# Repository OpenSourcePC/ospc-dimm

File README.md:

# ospc-dimm
Open Source DIMM modules.

For a contribution guide, see CONTRIBUTING.md

## Folder format

`ospc-ddr[ddr version]-[dimmtype]-[number of ranks]r-x[data bus width of modules, comma seperated if mixed]-[S if SPD only, T if SPD + temp sensor]`

## Subprojects

`✔️: done ❓: needs verification, ❌: not done`

Projects marked for verification may not function properly.

 * `ospc-ddr4-udimm-1r-x16-t` : UDIMM, DDR4, 1 rank, x16 (96ball), SPD+Temp (Schematic ❓, PCB ❌)

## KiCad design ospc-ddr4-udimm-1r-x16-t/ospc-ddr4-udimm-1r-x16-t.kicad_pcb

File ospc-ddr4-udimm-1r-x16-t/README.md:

# ospc-ddr4-udimm-1r-x16-t

To-dos:
 * Schem verification.
 * PCB routing & resistor/capacitor positioning.

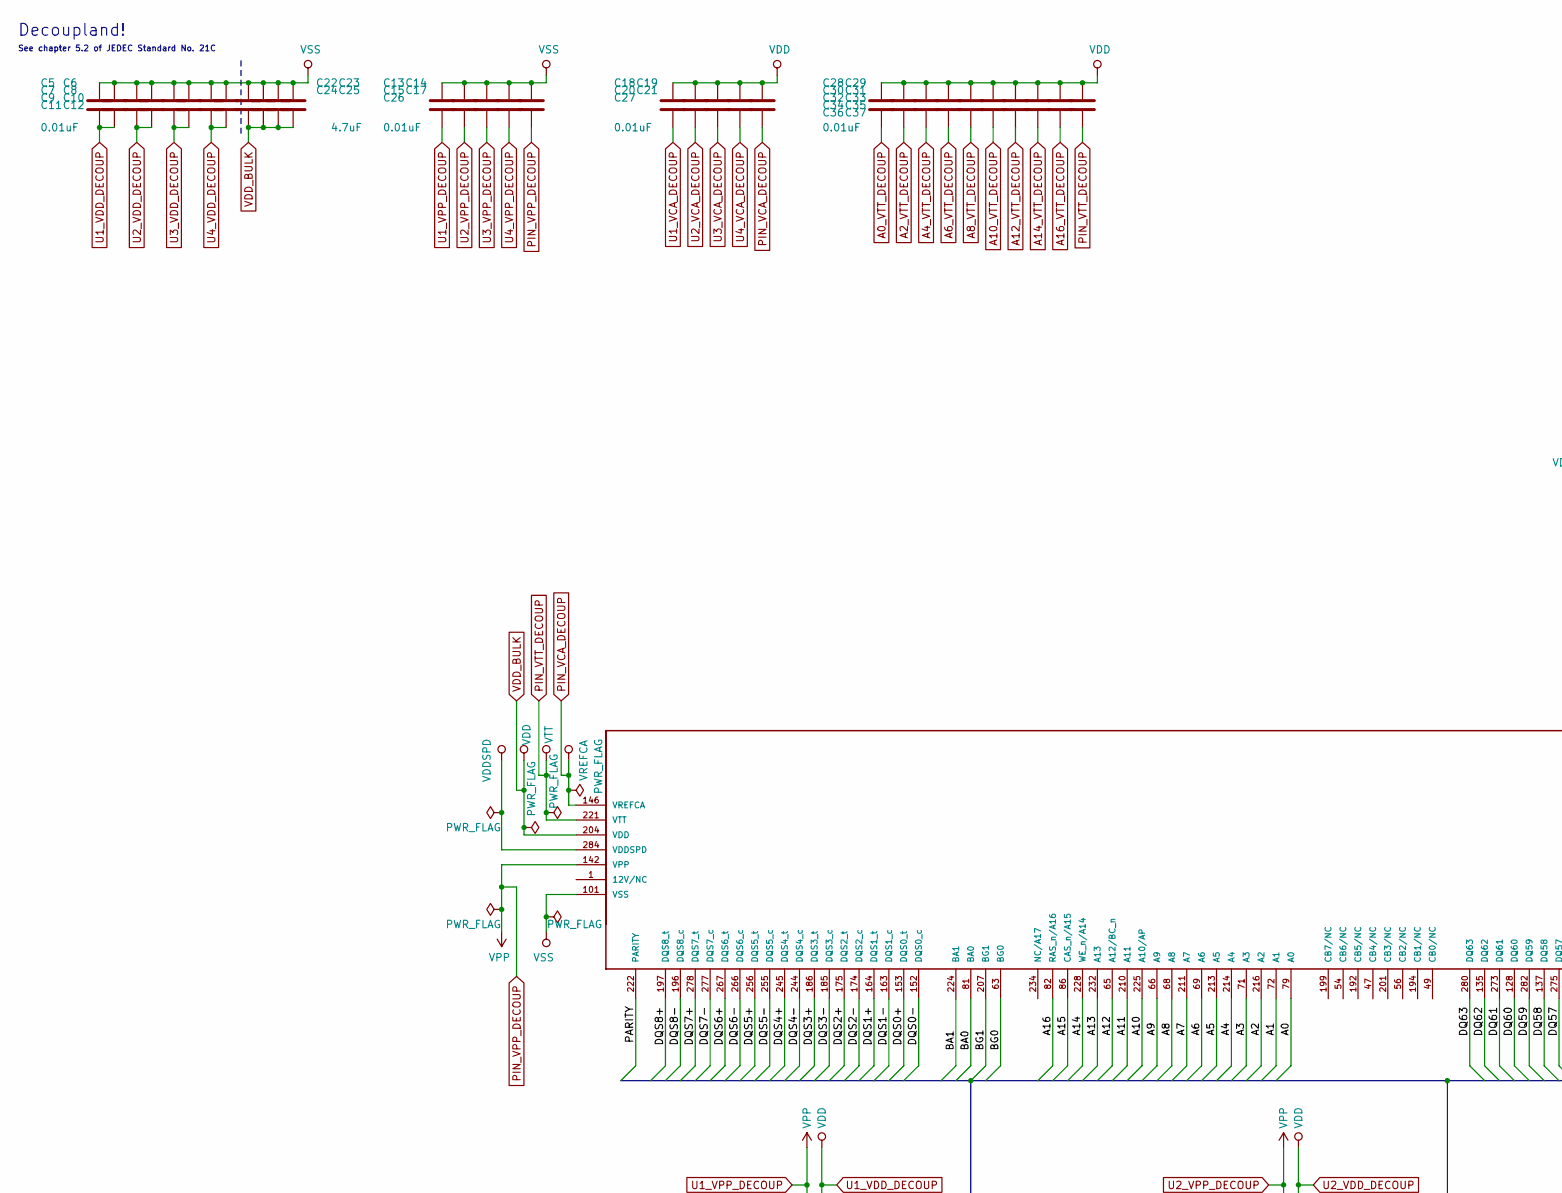
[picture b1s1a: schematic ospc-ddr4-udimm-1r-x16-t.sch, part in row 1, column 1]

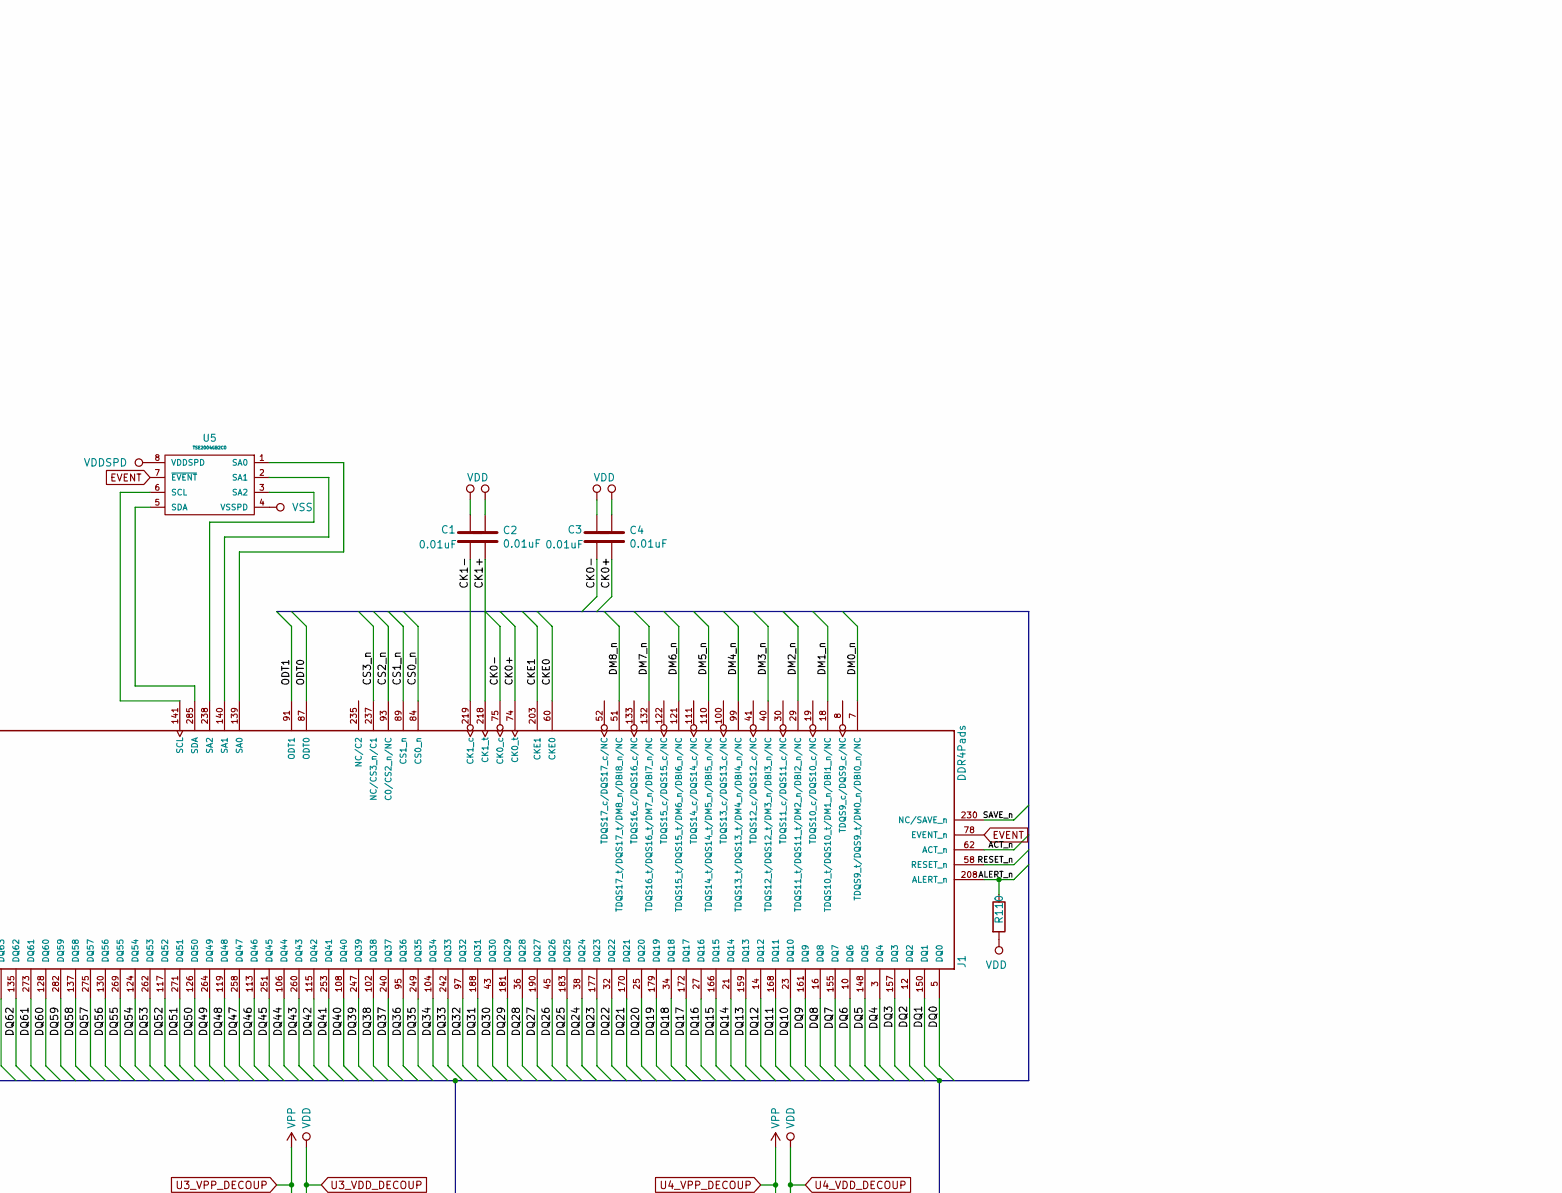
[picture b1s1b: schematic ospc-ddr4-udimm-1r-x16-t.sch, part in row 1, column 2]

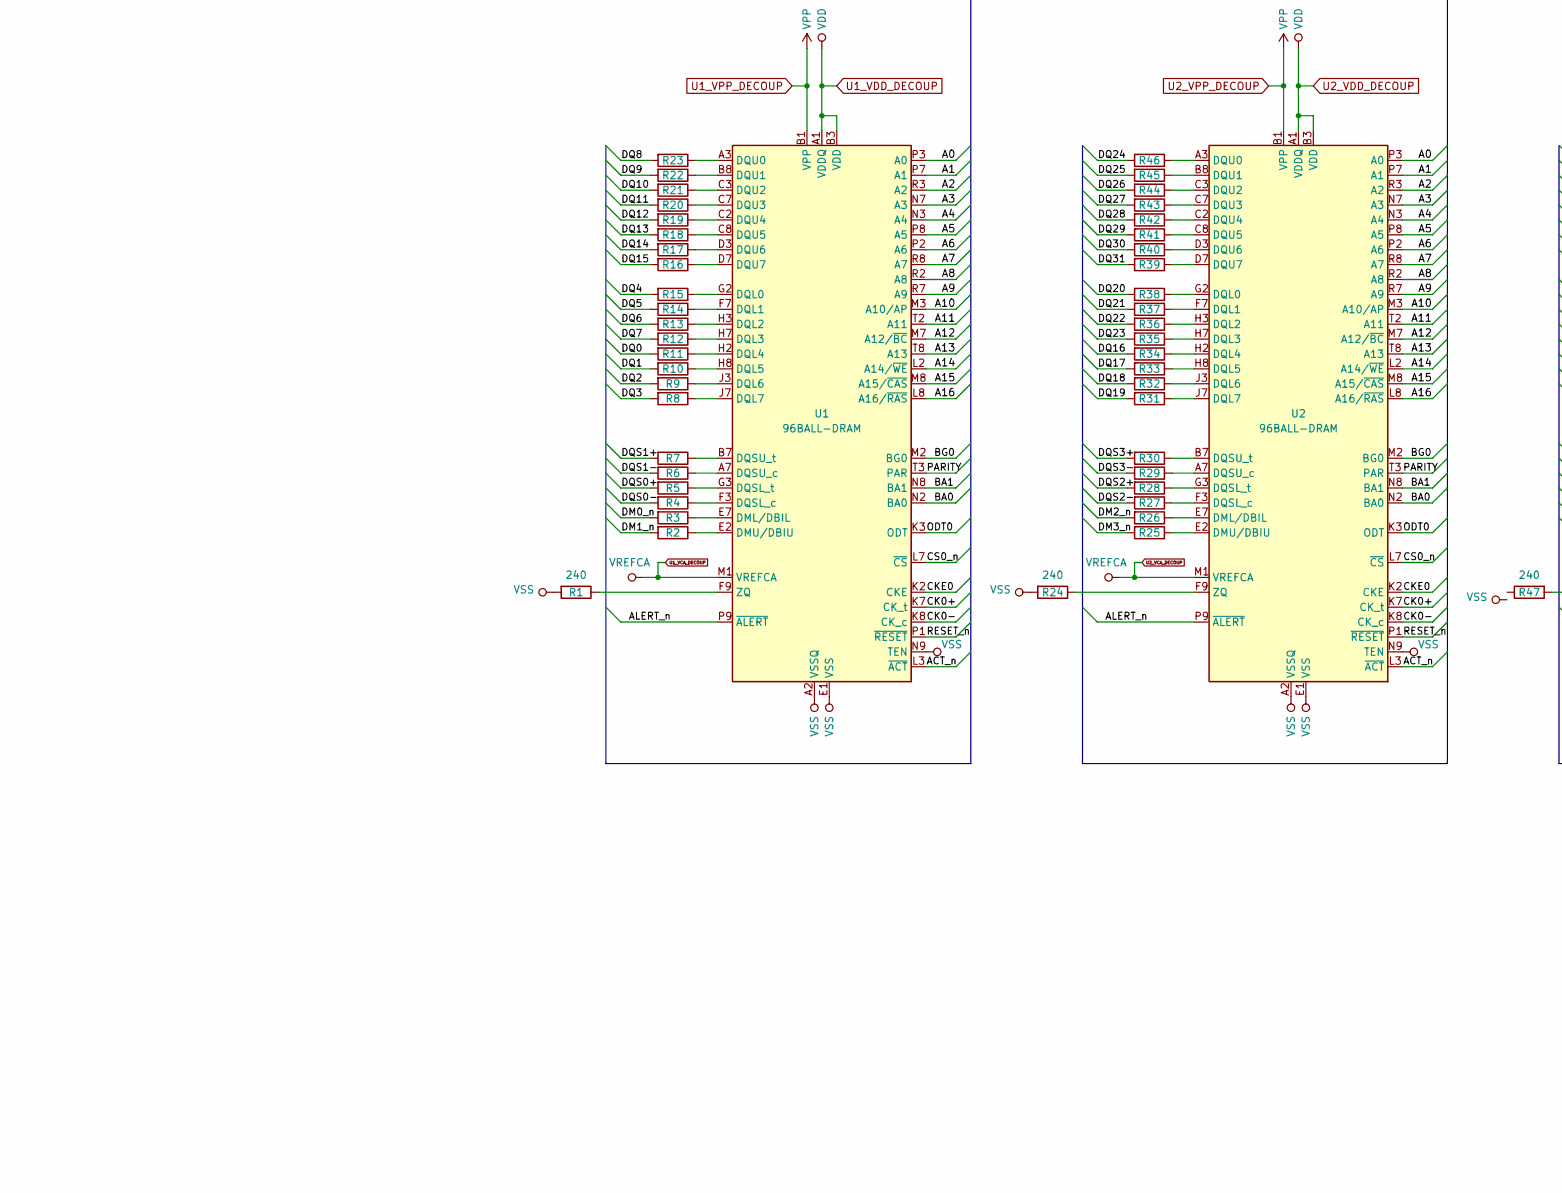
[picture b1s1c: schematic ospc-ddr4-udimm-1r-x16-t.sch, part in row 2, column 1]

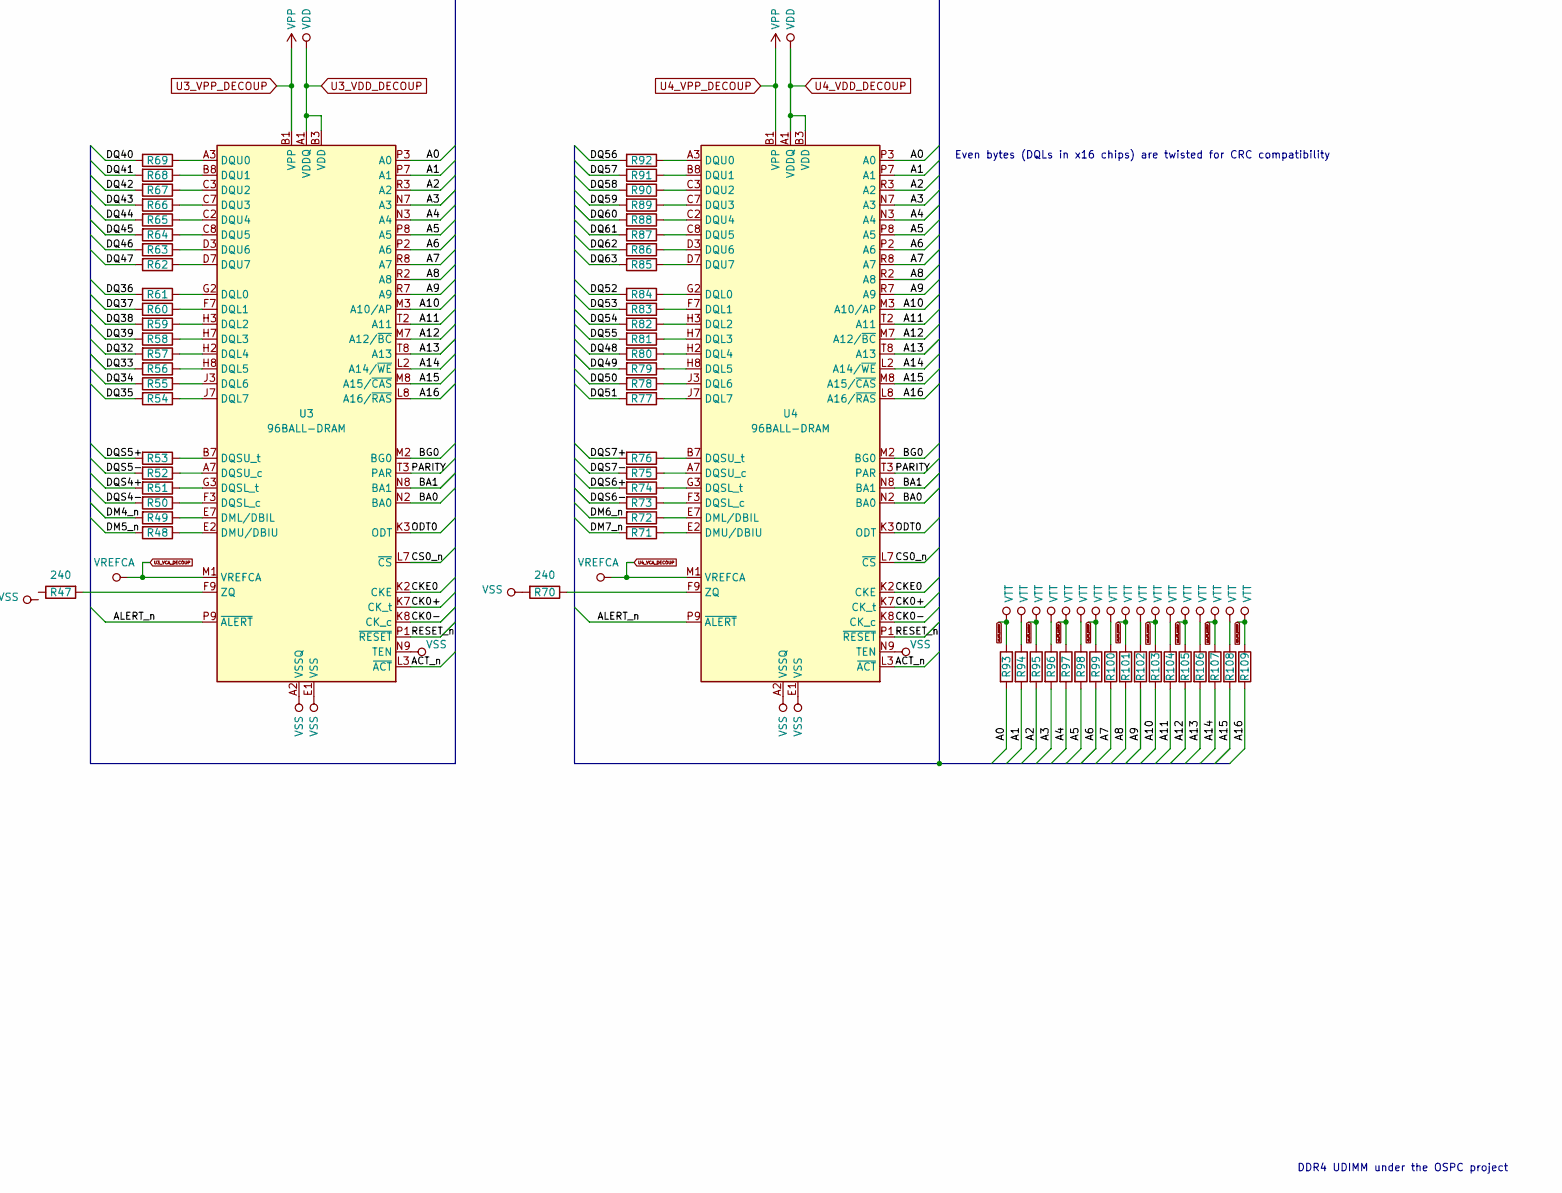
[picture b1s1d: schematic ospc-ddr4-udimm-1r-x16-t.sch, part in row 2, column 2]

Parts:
C1, C2, C3, C4, C5, C6, C7, C8, C9, C10, C11, C12, C13, C14, C15, C17, C18, C19, C20, C21, C26, C27, C28, C29, C30, C31, C32, C33, C34, C35, C36, C37: 0.01uF; C_0402_1005Metric
C22, C23, C24, C25: 4.7uF; C_0402_1005Metric
J1: DDR4Pads; DDR4_DIMM
R1, R24, R47, R70: 240; R_0402_1005Metric
R2, R3, R4, R5, R6, R7, R8, R9, R10, R11, R12, R13, R14, R15, R16, R17, R18, R19, R20, R21, R22, R23, R25, R26, R27, R28, R29, R30, R31, R32, R33, R34, R35, R36, R37, R38, R39, R40, R41, R42, R43, R44, R45, R46, R48, R49, R50, R51, R52, R53, R54, R55, R56, R57, R58, R59, R60, R61, R62, R63, R64, R65, R66, R67, R68, R69, R71, R72, R73, R74, R75, R76, R77, R78, R79, R80, R81, R82, R83, R84, R85, R86, R87, R88, R89, R90, R91, R92, R93, R94, R95, R96, R97, R98, R99, R100, R101, R102, R103, R104, R105, R106, R107, R108, R109, R110: 15; R_0402_1005Metric
U1, U2, U3, U4: 96BALL-DRAM; FBGA96
U5: TSE2004GB2C0; DFN-8-1EP_2x3mm_P0.5mm_EP0.61x2.2mm

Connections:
/A0: J1.79 (A0), R93.2, U1.P3 (A0), U2.P3 (A0), U3.P3 (A0), U4.P3 (A0)
/A1: J1.72 (A1), R94.2, U1.P7 (A1), U2.P7 (A1), U3.P7 (A1), U4.P7 (A1)
/A2: J1.216 (A2), R95.2, U1.R3 (A2), U2.R3 (A2), U3.R3 (A2), U4.R3 (A2)
/A3: J1.71 (A3), R96.2, U1.N7 (A3), U2.N7 (A3), U3.N7 (A3), U4.N7 (A3)
/A4: J1.214 (A4), R97.2, U1.N3 (A4), U2.N3 (A4), U3.N3 (A4), U4.N3 (A4)
/A5: J1.213 (A5), R98.2, U1.P8 (A5), U2.P8 (A5), U3.P8 (A5), U4.P8 (A5)
/A6: J1.69 (A6), R99.2, U1.P2 (A6), U2.P2 (A6), U3.P2 (A6), U4.P2 (A6)
/A7: J1.211 (A7), R100.2, U1.R8 (A7), U2.R8 (A7), U3.R8 (A7), U4.R8 (A7)
/A8: J1.68 (A8), R101.2, U1.R2 (A8), U2.R2 (A8), U3.R2 (A8), U4.R2 (A8)
/A9: J1.66 (A9), R102.2, U1.R7 (A9), U2.R7 (A9), U3.R7 (A9), U4.R7 (A9)
/A10: J1.225 (A10/AP), R103.2, U1.M3 (A10/AP), U2.M3 (A10/AP), U3.M3 (A10/AP), U4.M3 (A10/AP)
/A11: J1.210 (A11), R104.2, U1.T2 (A11), U2.T2 (A11), U3.T2 (A11), U4.T2 (A11)
/A12: J1.65 (A12/BC_n), R105.2, U1.M7 (A12/~BC), U2.M7 (A12/~BC), U3.M7 (A12/~BC), U4.M7 (A12/~BC)
/A13: J1.232 (A13), R106.2, U1.T8 (A13), U2.T8 (A13), U3.T8 (A13), U4.T8 (A13)
/A14: J1.228 (WE_n/A14), R107.2, U1.L2 (A14/~WE), U2.L2 (A14/~WE), U3.L2 (A14/~WE), U4.L2 (A14/~WE)
/A15: J1.86 (CAS_n/A15), R108.2, U1.M8 (A15/~CAS), U2.M8 (A15/~CAS), U3.M8 (A15/~CAS), U4.M8 (A15/~CAS)
/A16: J1.82 (RAS_n/A16), R109.2, U1.L8 (A16/~RAS), U2.L8 (A16/~RAS), U3.L8 (A16/~RAS), U4.L8 (A16/~RAS)
/ACT_n: J1.62 (ACT_n), U1.L3 (~ACT), U2.L3 (~ACT), U3.L3 (~ACT), U4.L3 (~ACT)
/ALERT_n: J1.208 (ALERT_n), R110.1, U1.P9 (~ALERT), U2.P9 (~ALERT), U3.P9 (~ALERT), U4.P9 (~ALERT)
/BA0: J1.81 (BA0), U1.N2 (BA0), U2.N2 (BA0), U3.N2 (BA0), U4.N2 (BA0)
/BA1: J1.224 (BA1), U1.N8 (BA1), U2.N8 (BA1), U3.N8 (BA1), U4.N8 (BA1)
/BG0: J1.63 (BG0), U1.M2 (BG0), U2.M2 (BG0), U3.M2 (BG0), U4.M2 (BG0)
/BG1: J1.207 (BG1)
/CK0+: C4.2, J1.74 (CK0_t), U1.K7 (CK_t), U2.K7 (CK_t), U3.K7 (CK_t), U4.K7 (CK_t)
/CK0-: C3.2, J1.75 (CK0_c), U1.K8 (CK_c), U2.K8 (CK_c), U3.K8 (CK_c), U4.K8 (CK_c)
/CK1+: C2.2, J1.218 (CK1_t)
/CK1-: C1.2, J1.219 (CK1_c)
/CKE0: J1.60 (CKE0), U1.K2 (CKE), U2.K2 (CKE), U3.K2 (CKE), U4.K2 (CKE)
/CKE1: J1.203 (CKE1)
/CS0_n: J1.84 (CS0_n), U1.L7 (~CS), U2.L7 (~CS), U3.L7 (~CS), U4.L7 (~CS)
/CS1_n: J1.89 (CS1_n)
/CS2_n: J1.93 (C0/CS2_n/NC)
/CS3_n: J1.237 (NC/CS3_n/C1)
/DM0_n: J1.7 (TDQS9_t/DQS9_t/DM0_n/DBI0_n/NC), R3.2
/DM1_n: J1.18 (TDQS10_t/DQS10_t/DM1_n/DBI1_n/NC), R2.2
/DM2_n: J1.29 (TDQS11_t/DQS11_t/DM2_n/DBI2_n/NC), R26.2
/DM3_n: J1.40 (TDQS12_t/DQS12_t/DM3_n/DBI3_n/NC), R25.2
/DM4_n: J1.99 (TDQS13_t/DQS13_t/DM4_n/DBI4_n/NC), R49.2
/DM5_n: J1.110 (TDQS14_t/DQS14_t/DM5_n/DBI5_n/NC), R48.2
/DM6_n: J1.121 (TDQS15_t/DQS15_t/DM6_n/DBI6_n/NC), R72.2
/DM7_n: J1.132 (TDQS16_t/DQS16_t/DM7_n/DBI7_n/NC), R71.2
/DM8_n: J1.51 (TDQS17_t/DQS17_t/DM8_n/DBI8_n/NC)
/DQ0: J1.5 (DQ0), R11.2
/DQ1: J1.150 (DQ1), R10.2
/DQ2: J1.12 (DQ2), R9.2
/DQ3: J1.157 (DQ3), R8.2
/DQ4: J1.3 (DQ4), R15.2
/DQ5: J1.148 (DQ5), R14.2
/DQ6: J1.10 (DQ6), R13.2
/DQ7: J1.155 (DQ7), R12.2
/DQ8: J1.16 (DQ8), R23.2
/DQ9: J1.161 (DQ9), R22.2
/DQ10: J1.23 (DQ10), R21.2
/DQ11: J1.168 (DQ11), R20.2
/DQ12: J1.14 (DQ12), R19.2
/DQ13: J1.159 (DQ13), R18.2
/DQ14: J1.21 (DQ14), R17.2
/DQ15: J1.166 (DQ15), R16.2
/DQ16: J1.27 (DQ16), R34.2
/DQ17: J1.172 (DQ17), R33.2
/DQ18: J1.34 (DQ18), R32.2
/DQ19: J1.179 (DQ19), R31.2
/DQ20: J1.25 (DQ20), R38.2
/DQ21: J1.170 (DQ21), R37.2
/DQ22: J1.32 (DQ22), R36.2
/DQ23: J1.177 (DQ23), R35.2
/DQ24: J1.38 (DQ24), R46.2
/DQ25: J1.183 (DQ25), R45.2
/DQ26: J1.45 (DQ26), R44.2
/DQ27: J1.190 (DQ27), R43.2
/DQ28: J1.36 (DQ28), R42.2
/DQ29: J1.181 (DQ29), R41.2
/DQ30: J1.43 (DQ30), R40.2
/DQ31: J1.188 (DQ31), R39.2
/DQ32: J1.97 (DQ32), R57.2
/DQ33: J1.242 (DQ33), R56.2
/DQ34: J1.104 (DQ34), R55.1
/DQ35: J1.249 (DQ35), R54.2
/DQ36: J1.95 (DQ36), R61.2
/DQ37: J1.240 (DQ37), R60.2
/DQ38: J1.102 (DQ38), R59.2
/DQ39: J1.247 (DQ39), R58.2
/DQ40: J1.108 (DQ40), R69.2
/DQ41: J1.253 (DQ41), R68.2
/DQ42: J1.115 (DQ42), R67.2
/DQ43: J1.260 (DQ43), R66.2
/DQ44: J1.106 (DQ44), R65.2
/DQ45: J1.251 (DQ45), R64.2
/DQ46: J1.113 (DQ46), R63.2
/DQ47: J1.258 (DQ47), R62.2
/DQ48: J1.119 (DQ48), R80.2
/DQ49: J1.264 (DQ49), R79.2
/DQ50: J1.126 (DQ50), R78.2
/DQ51: J1.271 (DQ51), R77.2
/DQ52: J1.117 (DQ52), R84.2
/DQ53: J1.262 (DQ53), R83.2
/DQ54: J1.124 (DQ54), R82.2
/DQ55: J1.269 (DQ55), R81.2
/DQ56: J1.130 (DQ56), R92.2
/DQ57: J1.275 (DQ57), R91.2
/DQ58: J1.137 (DQ58), R90.2
/DQ59: J1.282 (DQ59), R89.2
/DQ60: J1.128 (DQ60), R88.2
/DQ61: J1.273 (DQ61), R87.2
/DQ62: J1.135 (DQ62), R86.2
/DQ63: J1.280 (DQ63), R85.2
/DQS0+: J1.153 (DQS0_t), R5.2
/DQS0-: J1.152 (DQS0_c), R4.2
/DQS1+: J1.164 (DQS1_t), R7.2
/DQS1-: J1.163 (DQS1_c), R6.2
/DQS2+: J1.175 (DQS2_t), R28.2
/DQS2-: J1.174 (DQS2_c), R27.2
/DQS3+: J1.186 (DQS3_t), R30.2
/DQS3-: J1.185 (DQS3_c), R29.2
/DQS4+: J1.245 (DQS4_t), R51.2
/DQS4-: J1.244 (DQS4_c), R50.2
/DQS5+: J1.256 (DQS5_t), R53.2
/DQS5-: J1.255 (DQS5_c), R52.2
/DQS6+: J1.267 (DQS6_t), R74.2
/DQS6-: J1.266 (DQS6_c), R73.2
/DQS7+: J1.278 (DQS7_t), R76.2
/DQS7-: J1.277 (DQS7_c), R75.2
/DQS8+: J1.197 (DQS8_t)
/DQS8-: J1.196 (DQS8_c)
/ODT0: J1.87 (ODT0), U1.K3 (ODT), U2.K3 (ODT), U3.K3 (ODT), U4.K3 (ODT)
/ODT1: J1.91 (ODT1)
/PARITY: J1.222 (PARITY), U1.T3 (PAR), U2.T3 (PAR), U3.T3 (PAR), U4.T3 (PAR)
/RESET_n: J1.58 (RESET_n), U1.P1 (~RESET), U2.P1 (~RESET), U3.P1 (~RESET), U4.P1 (~RESET)
/SAVE_n: J1.230 (NC/SAVE_n)
A0_VTT_DECOUP: C28.2, C29.2, C30.2, C31.2, C32.2, C33.2, C34.2, C35.2, C36.2, C37.2, J1.77 (VTT), J1.221 (VTT), R93.1, R94.1, R95.1, R96.1, R97.1, R98.1, R99.1, R100.1, R101.1, R102.1, R103.1, R104.1, R105.1, R106.1, R107.1, R108.1, R109.1
EVENT: J1.78 (EVENT_n), U5.7 (~EVENT)
unnamed: J1.1 (12V/NC), J1.145 (12V/NC)
unnamed: J1.139 (SA0), U5.1 (SA0)
unnamed: J1.140 (SA1), U5.2 (SA1)
unnamed: J1.141 (SCL), U5.6 (SCL)
unnamed: J1.144 (RFU), J1.205 (RFU), J1.227 (RFU)
unnamed: J1.238 (SA2), U5.3 (SA2)
unnamed: J1.285 (SDA), U5.5 (SDA)
unnamed: R1.1, U1.F9 (ZQ)
unnamed: R2.1, U1.E2 (DMU/DBIU)
unnamed: R3.1, U1.E7 (DML/DBIL)
unnamed: R4.1, U1.F3 (DQSL_c)
unnamed: R5.1, U1.G3 (DQSL_t)
unnamed: R6.1, U1.A7 (DQSU_c)
unnamed: R7.1, U1.B7 (DQSU_t)
unnamed: R8.1, U1.J7 (DQL7)
unnamed: R9.1, U1.J3 (DQL6)
unnamed: R10.1, U1.H8 (DQL5)
unnamed: R11.1, U1.H2 (DQL4)
unnamed: R12.1, U1.H7 (DQL3)
unnamed: R13.1, U1.H3 (DQL2)
unnamed: R14.1, U1.F7 (DQL1)
unnamed: R15.1, U1.G2 (DQL0)
unnamed: R16.1, U1.D7 (DQU7)
unnamed: R17.1, U1.D3 (DQU6)
unnamed: R18.1, U1.C8 (DQU5)
unnamed: R19.1, U1.C2 (DQU4)
unnamed: R20.1, U1.C7 (DQU3)
unnamed: R21.1, U1.C3 (DQU2)
unnamed: R22.1, U1.B8 (DQU1)
unnamed: R23.1, U1.A3 (DQU0)
unnamed: R24.1, U2.F9 (ZQ)
unnamed: R25.1, U2.E2 (DMU/DBIU)
unnamed: R26.1, U2.E7 (DML/DBIL)
unnamed: R27.1, U2.F3 (DQSL_c)
unnamed: R28.1, U2.G3 (DQSL_t)
unnamed: R29.1, U2.A7 (DQSU_c)
unnamed: R30.1, U2.B7 (DQSU_t)
unnamed: R31.1, U2.J7 (DQL7)
unnamed: R32.1, U2.J3 (DQL6)
unnamed: R33.1, U2.H8 (DQL5)
unnamed: R34.1, U2.H2 (DQL4)
unnamed: R35.1, U2.H7 (DQL3)
unnamed: R36.1, U2.H3 (DQL2)
unnamed: R37.1, U2.F7 (DQL1)
unnamed: R38.1, U2.G2 (DQL0)
unnamed: R39.1, U2.D7 (DQU7)
unnamed: R40.1, U2.D3 (DQU6)
unnamed: R41.1, U2.C8 (DQU5)
unnamed: R42.1, U2.C2 (DQU4)
unnamed: R43.1, U2.C7 (DQU3)
unnamed: R44.1, U2.C3 (DQU2)
unnamed: R45.1, U2.B8 (DQU1)
unnamed: R46.1, U2.A3 (DQU0)
unnamed: R47.2, U3.F9 (ZQ)
unnamed: R48.1, U3.E2 (DMU/DBIU)
unnamed: R49.1, U3.E7 (DML/DBIL)
unnamed: R50.1, U3.F3 (DQSL_c)
unnamed: R51.1, U3.G3 (DQSL_t)
unnamed: R52.1, U3.A7 (DQSU_c)
unnamed: R53.1, U3.B7 (DQSU_t)
unnamed: R54.1, U3.J7 (DQL7)
unnamed: R55.2, U3.J3 (DQL6)
unnamed: R56.1, U3.H8 (DQL5)
unnamed: R57.1, U3.H2 (DQL4)
unnamed: R58.1, U3.H7 (DQL3)
unnamed: R59.1, U3.H3 (DQL2)
unnamed: R60.1, U3.F7 (DQL1)
unnamed: R61.1, U3.G2 (DQL0)
unnamed: R62.1, U3.D7 (DQU7)
unnamed: R63.1, U3.D3 (DQU6)
unnamed: R64.1, U3.C8 (DQU5)
unnamed: R65.1, U3.C2 (DQU4)
unnamed: R66.1, U3.C7 (DQU3)
unnamed: R67.1, U3.C3 (DQU2)
unnamed: R68.1, U3.B8 (DQU1)
unnamed: R69.1, U3.A3 (DQU0)
unnamed: R70.1, U4.F9 (ZQ)
unnamed: R71.1, U4.E2 (DMU/DBIU)
unnamed: R72.1, U4.E7 (DML/DBIL)
unnamed: R73.1, U4.F3 (DQSL_c)
unnamed: R74.1, U4.G3 (DQSL_t)
unnamed: R75.1, U4.A7 (DQSU_c)
unnamed: R76.1, U4.B7 (DQSU_t)
unnamed: R77.1, U4.J7 (DQL7)
unnamed: R78.1, U4.J3 (DQL6)
unnamed: R79.1, U4.H8 (DQL5)
unnamed: R80.1, U4.H2 (DQL4)
unnamed: R81.1, U4.H7 (DQL3)
unnamed: R82.1, U4.H3 (DQL2)
unnamed: R83.1, U4.F7 (DQL1)
unnamed: R84.1, U4.G2 (DQL0)
unnamed: R85.1, U4.D7 (DQU7)
unnamed: R86.1, U4.D3 (DQU6)
unnamed: R87.1, U4.C8 (DQU5)
unnamed: R88.1, U4.C2 (DQU4)
unnamed: R89.1, U4.C7 (DQU3)
unnamed: R90.1, U4.C3 (DQU2)
unnamed: R91.1, U4.B8 (DQU1)
unnamed: R92.1, U4.A3 (DQU0)
PIN_VCA_DECOUP: C18.2, C19.2, C20.2, C21.2, C27.2, J1.146 (VREFCA), U1.M1 (VREFCA), U2.M1 (VREFCA), U3.M1 (VREFCA), U4.M1 (VREFCA)
PIN_VPP_DECOUP: C13.2, C14.2, C15.2, C17.2, C26.2, J1.142 (VPP), J1.143 (VPP), J1.286 (VPP), J1.287 (VPP), J1.288 (VPP), U1.B1 (VPP), U1.R9 (VPP), U2.B1 (VPP), U2.R9 (VPP), U3.B1 (VPP), U3.R9 (VPP), U4.B1 (VPP), U4.R9 (VPP)
U1_VDD_DECOUP: C1.1, C2.1, C3.1, C4.1, C5.2, C6.2, C7.2, C8.2, C9.2, C10.2, C11.2, C12.2, C18.1, C19.1, C20.1, C21.1, C22.2, C23.2, C24.2, C25.2, C27.1, C28.1, C29.1, C30.1, C31.1, C32.1, C33.1, C34.1, C35.1, C36.1, C37.1, J1.59 (VDD), J1.61 (VDD), J1.64 (VDD), J1.67 (VDD), J1.70 (VDD), J1.73 (VDD), J1.76 (VDD), J1.80 (VDD), J1.83 (VDD), J1.85 (VDD), J1.88 (VDD), J1.90 (VDD), J1.92 (VDD), J1.204 (VDD), J1.206 (VDD), J1.209 (VDD), J1.212 (VDD), J1.215 (VDD), J1.217 (VDD), J1.220 (VDD), J1.223 (VDD), J1.226 (VDD), J1.229 (VDD), J1.231 (VDD), J1.233 (VDD), J1.236 (VDD), R110.2, U1.A1 (VDDQ), U1.A9 (VDDQ), U1.B3 (VDD), U1.B9 (VDD), U1.C1 (VDDQ), U1.D1 (VDD), U1.D9 (VDDQ), U1.F2 (VDDQ), U1.F8 (VDDQ), U1.G1 (VDDQ), U1.G7 (VDD), U1.G9 (VDDQ), U1.J1 (VDD), U1.J2 (VDDQ), U1.J8 (VDDQ), U1.J9 (VDD), U1.L1 (VDD), U1.L9 (VDD), U1.R1 (VDD), U1.T9 (VDD), U2.A1 (VDDQ), U2.A9 (VDDQ), U2.B3 (VDD), U2.B9 (VDD), U2.C1 (VDDQ), U2.D1 (VDD), U2.D9 (VDDQ), U2.F2 (VDDQ), U2.F8 (VDDQ), U2.G1 (VDDQ), U2.G7 (VDD), U2.G9 (VDDQ), U2.J1 (VDD), U2.J2 (VDDQ), U2.J8 (VDDQ), U2.J9 (VDD), U2.L1 (VDD), U2.L9 (VDD), U2.R1 (VDD), U2.T9 (VDD), U3.A1 (VDDQ), U3.A9 (VDDQ), U3.B3 (VDD), U3.B9 (VDD), U3.C1 (VDDQ), U3.D1 (VDD), U3.D9 (VDDQ), U3.F2 (VDDQ), U3.F8 (VDDQ), U3.G1 (VDDQ), U3.G7 (VDD), U3.G9 (VDDQ), U3.J1 (VDD), U3.J2 (VDDQ), U3.J8 (VDDQ), U3.J9 (VDD), U3.L1 (VDD), U3.L9 (VDD), U3.R1 (VDD), U3.T9 (VDD), U4.A1 (VDDQ), U4.A9 (VDDQ), U4.B3 (VDD), U4.B9 (VDD), U4.C1 (VDDQ), U4.D1 (VDD), U4.D9 (VDDQ), U4.F2 (VDDQ), U4.F8 (VDDQ), U4.G1 (VDDQ), U4.G7 (VDD), U4.G9 (VDDQ), U4.J1 (VDD), U4.J2 (VDDQ), U4.J8 (VDDQ), U4.J9 (VDD), U4.L1 (VDD), U4.L9 (VDD), U4.R1 (VDD), U4.T9 (VDD)
VDDSPD: J1.284 (VDDSPD), U5.8 (VDDSPD)
VSS: C5.1, C6.1, C7.1, C8.1, C9.1, C10.1, C11.1, C12.1, C13.1, C14.1, C15.1, C17.1, C22.1, C23.1, C24.1, C25.1, C26.1, J1.2 (VSS), J1.4 (VSS), J1.6 (VSS), J1.9 (VSS), J1.11 (VSS), J1.13 (VSS), J1.15 (VSS), J1.17 (VSS), J1.20 (VSS), J1.22 (VSS), J1.24 (VSS), J1.26 (VSS), J1.28 (VSS), J1.31 (VSS), J1.33 (VSS), J1.35 (VSS), J1.37 (VSS), J1.39 (VSS), J1.42 (VSS), J1.44 (VSS), J1.46 (VSS), J1.48 (VSS), J1.50 (VSS), J1.53 (VSS), J1.55 (VSS), J1.57 (VSS), J1.94 (VSS), J1.96 (VSS), J1.98 (VSS), J1.101 (VSS), J1.103 (VSS), J1.105 (VSS), J1.107 (VSS), J1.109 (VSS), J1.112 (VSS), J1.114 (VSS), J1.116 (VSS), J1.118 (VSS), J1.120 (VSS), J1.123 (VSS), J1.125 (VSS), J1.127 (VSS), J1.129 (VSS), J1.131 (VSS), J1.134 (VSS), J1.136 (VSS), J1.138 (VSS), J1.147 (VSS), J1.149 (VSS), J1.151 (VSS), J1.154 (VSS), J1.156 (VSS), J1.158 (VSS), J1.160 (VSS), J1.162 (VSS), J1.165 (VSS), J1.167 (VSS), J1.169 (VSS), J1.171 (VSS), J1.173 (VSS), J1.176 (VSS), J1.178 (VSS), J1.180 (VSS), J1.182 (VSS), J1.184 (VSS), J1.187 (VSS), J1.189 (VSS), J1.191 (VSS), J1.193 (VSS), J1.195 (VSS), J1.198 (VSS), J1.200 (VSS), J1.202 (VSS), J1.239 (VSS), J1.241 (VSS), J1.243 (VSS), J1.246 (VSS), J1.248 (VSS), J1.250 (VSS), J1.252 (VSS), J1.254 (VSS), J1.257 (VSS), J1.259 (VSS), J1.261 (VSS), J1.263 (VSS), J1.265 (VSS), J1.268 (VSS), J1.270 (VSS), J1.272 (VSS), J1.274 (VSS), J1.276 (VSS), J1.279 (VSS), J1.281 (VSS), J1.283 (VSS), R1.2, R24.2, R70.2, U1.A2 (VSSQ), U1.A8 (VSSQ), U1.B2 (VSS), U1.C9 (VSSQ), U1.D2 (VSSQ), U1.D8 (VSSQ), U1.E1 (VSS), U1.E3 (VSSQ), U1.E8 (VSSQ), U1.E9 (VSS), U1.F1 (VSSQ), U1.G8 (VSS), U1.H1 (VSSQ), U1.H9 (VSSQ), U1.K1 (VSS), U1.K9 (VSS), U1.M9 (VSS), U1.N1 (VSS), U1.N9 (TEN), U1.T1 (VSS), U2.A2 (VSSQ), U2.A8 (VSSQ), U2.B2 (VSS), U2.C9 (VSSQ), U2.D2 (VSSQ), U2.D8 (VSSQ), U2.E1 (VSS), U2.E3 (VSSQ), U2.E8 (VSSQ), U2.E9 (VSS), U2.F1 (VSSQ), U2.G8 (VSS), U2.H1 (VSSQ), U2.H9 (VSSQ), U2.K1 (VSS), U2.K9 (VSS), U2.M9 (VSS), U2.N1 (VSS), U2.N9 (TEN), U2.T1 (VSS), U3.A2 (VSSQ), U3.A8 (VSSQ), U3.B2 (VSS), U3.C9 (VSSQ), U3.D2 (VSSQ), U3.D8 (VSSQ), U3.E1 (VSS), U3.E3 (VSSQ), U3.E8 (VSSQ), U3.E9 (VSS), U3.F1 (VSSQ), U3.G8 (VSS), U3.H1 (VSSQ), U3.H9 (VSSQ), U3.K1 (VSS), U3.K9 (VSS), U3.M9 (VSS), U3.N1 (VSS), U3.N9 (TEN), U3.T1 (VSS), U4.A2 (VSSQ), U4.A8 (VSSQ), U4.B2 (VSS), U4.C9 (VSSQ), U4.D2 (VSSQ), U4.D8 (VSSQ), U4.E1 (VSS), U4.E3 (VSSQ), U4.E8 (VSSQ), U4.E9 (VSS), U4.F1 (VSSQ), U4.G8 (VSS), U4.H1 (VSSQ), U4.H9 (VSSQ), U4.K1 (VSS), U4.K9 (VSS), U4.M9 (VSS), U4.N1 (VSS), U4.N9 (TEN), U4.T1 (VSS), U5.4 (VSSPD)

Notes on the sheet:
DDR4 UDIMM under the OSPC project
See chapter 5.2 of JEDEC Standard No. 21C
Decoupland!
Even bytes (DQLs in x16 chips) are twisted for CRC compatibility

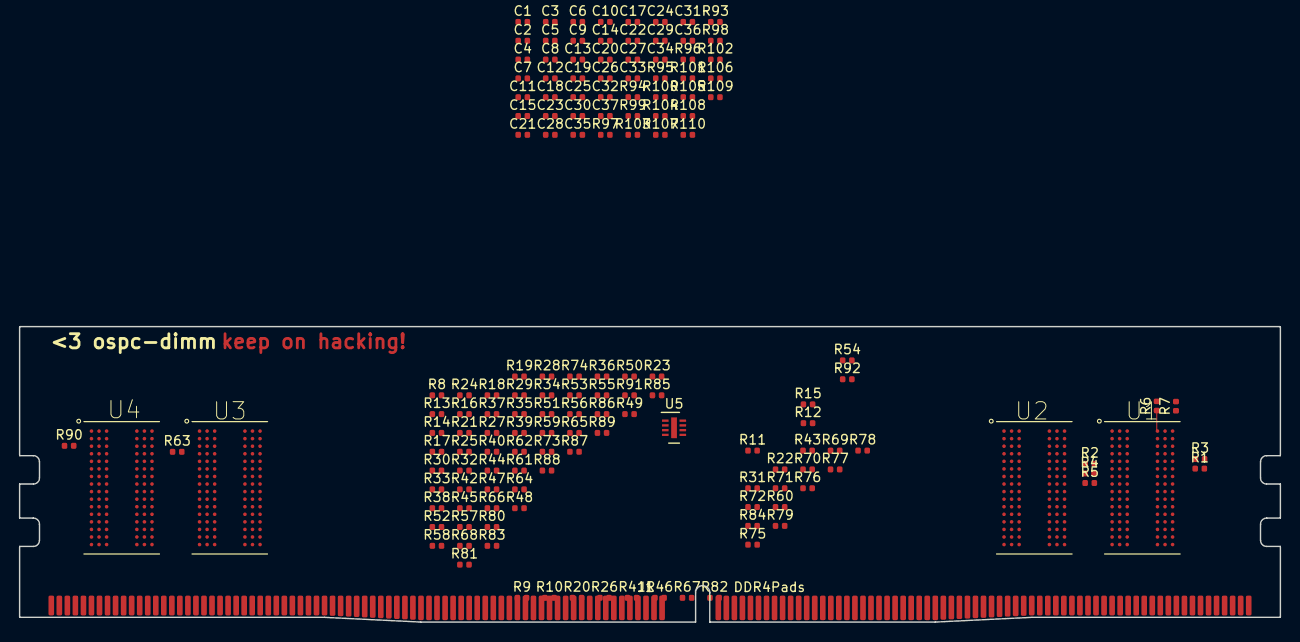
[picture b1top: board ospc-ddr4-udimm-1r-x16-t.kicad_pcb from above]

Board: 4 copper layers, 133.3 x 31.2 mm, 152 parts (0 on the bottom side), 225 nets.

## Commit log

2020-03-21 Added project structure and ddr4-udimm-1r-x16-t 🎉
